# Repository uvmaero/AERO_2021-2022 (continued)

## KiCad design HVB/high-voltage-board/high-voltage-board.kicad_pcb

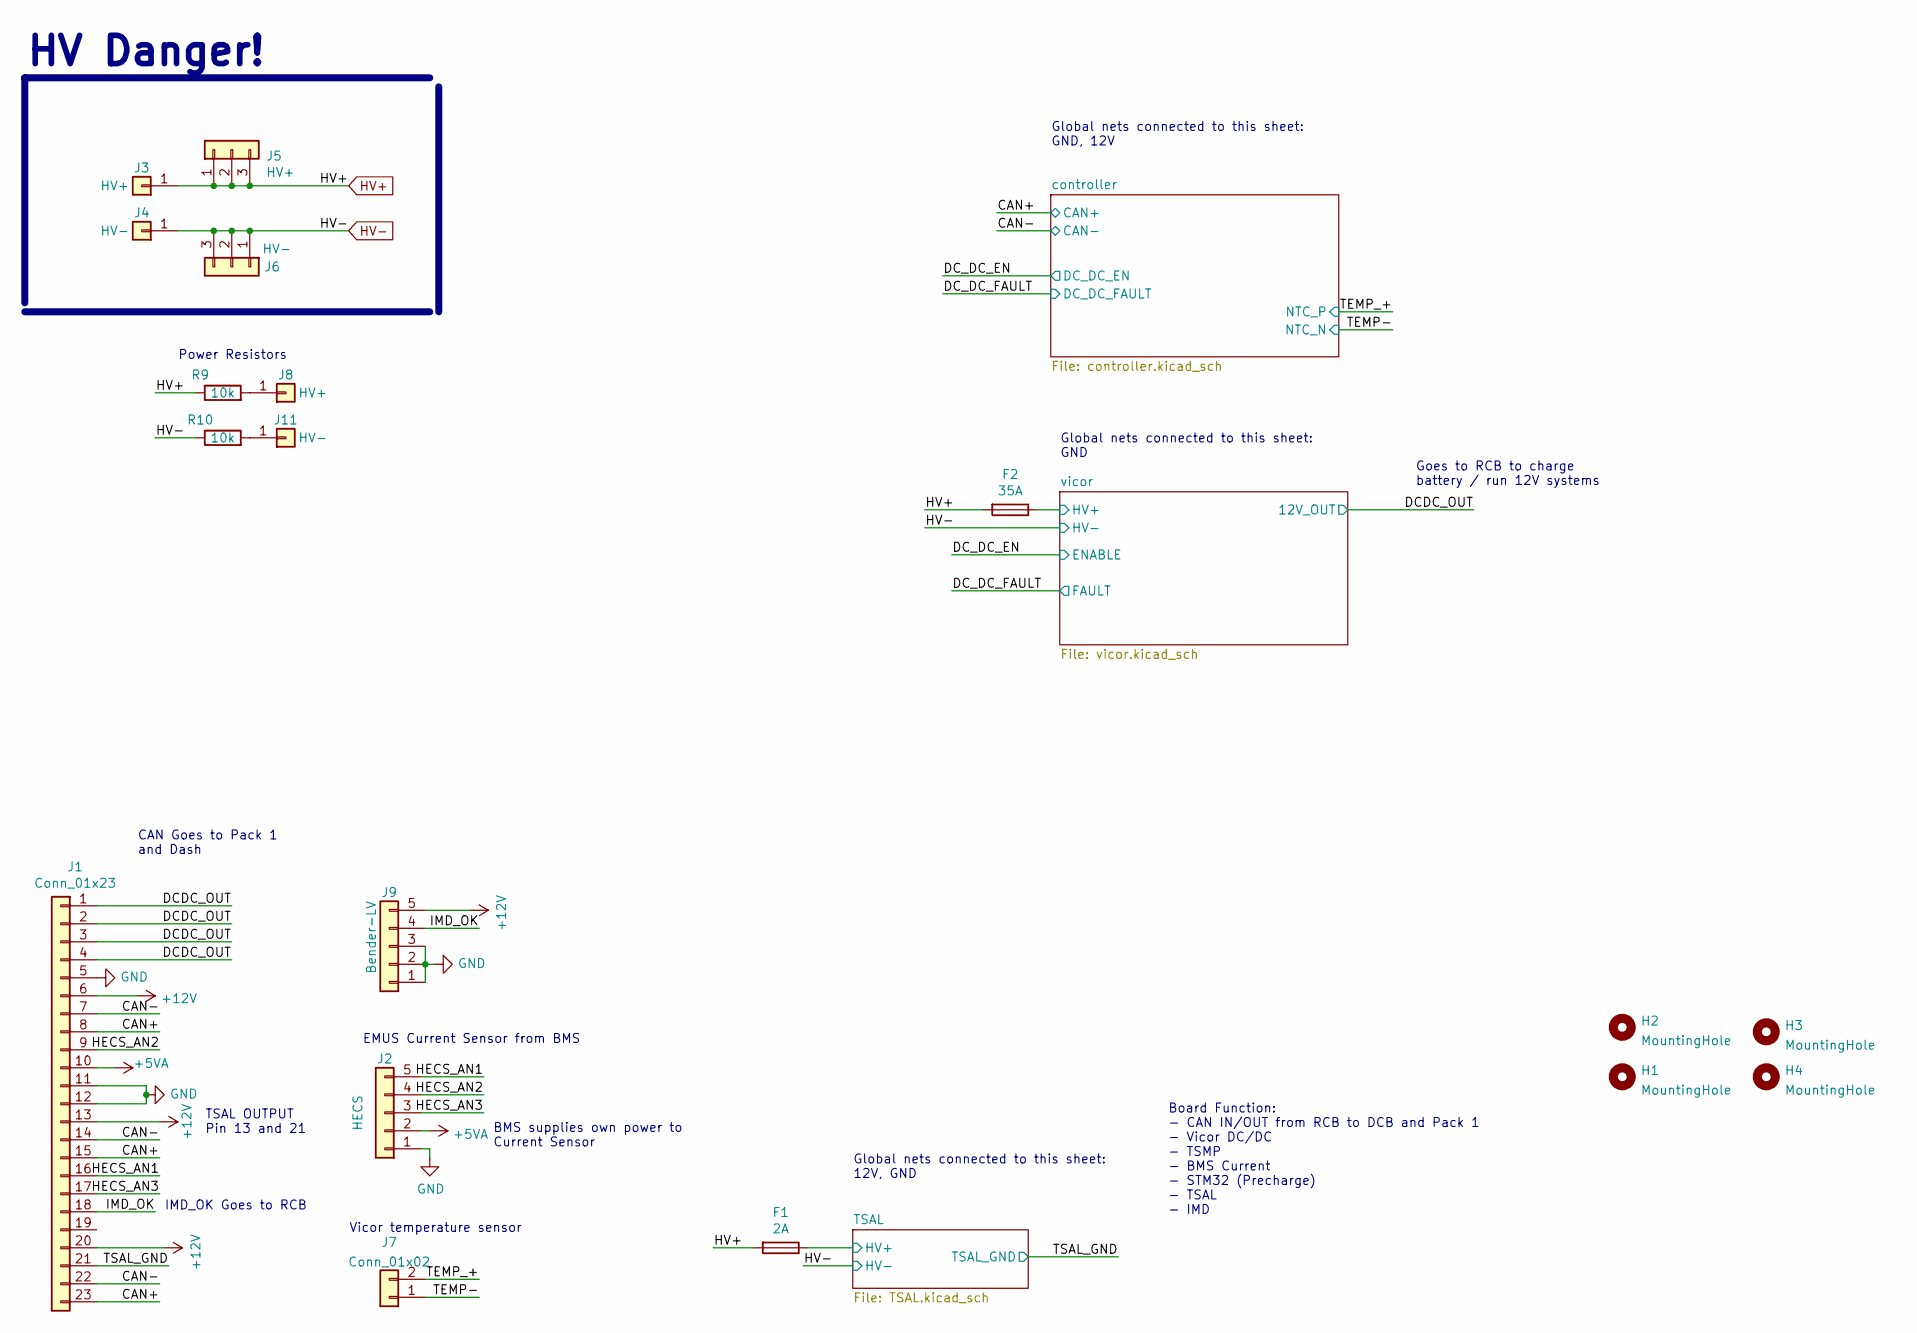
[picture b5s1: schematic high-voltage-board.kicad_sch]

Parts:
F1: 2A; Fuseholder_Cylinder-5x20mm_Schurter_0031_8201_Horizontal_Op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
F2: 35A; Fuseholder_Cylinder-5x20mm_Schurter_0031_8201_Horizontal_Op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
H1, H2, H3, H4: MountingHole; MountingHole_3.2mm_M3
J1: Conn_01x23; TE_1-770669-1_23pin_Horizontal
J2: HECS; JST_XH_B5B-XH-A_1x05_P2.50mm_Vertical
J3, J8: HV+; Hirose_DF63M-1P-3.96DSA_1x01_P3.96mm_Vertical
J4, J11: HV-; Hirose_DF63M-1P-3.96DSA_1x01_P3.96mm_Vertical
J5: HV+; TE_MATE-N-LOK_1-770870-x_1x03_P4.14mm_Vertical
J6: HV-; TE_MATE-N-LOK_1-770870-x_1x03_P4.14mm_Vertical
J7: Conn_01x02; JST_XH_B2B-XH-A_1x02_P2.50mm_Vertical
J9: Bender-LV; JST_XH_B5B-XH-A_1x05_P2.50mm_Vertical
R9, R10: 10k; R_Axial_Power_L50.0mm_W9.0mm_P60.96mm

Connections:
+3V3: J7.2; also elsewhere on the board
+5VA: J1.10, J2.2
+12V: J1.6, J1.13, J1.20, J9.5; also elsewhere on the board
/CAN+: J1.8, J1.15, J1.23; also elsewhere on the board
/CAN-: J1.7, J1.14, J1.22; also elsewhere on the board
/DCDC_OUT: J1.1, J1.2, J1.3, J1.4; also elsewhere on the board
/HECS_AN1: J1.16, J2.5
/HECS_AN2: J1.9, J2.4
/HECS_AN3: J1.17, J2.3
/IMD_OK: J1.18, J9.4
/TEMP-: J7.1; also elsewhere on the board
/TSAL/HV+: F1.1; also elsewhere on the board
/TSAL_GND: J1.21; also elsewhere on the board
/vicor/HV+: F2.1; also elsewhere on the board
GND: J1.5, J1.11, J1.12, J2.1, J9.1, J9.2, J9.3; also elsewhere on the board
HV+: F1.2, F2.2, J3.1, J5.1, J5.2, J5.3, R9.1
HV-: J4.1, J6.1, J6.2, J6.3, R10.1; also elsewhere on the board
unnamed: J8.1, R9.2
unnamed: J11.1, R10.2

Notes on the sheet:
Global nets connected to this sheet: GND, 12V
Global nets connected to this sheet: 12V, GND
IMD_OK Goes to RCB
Goes to RCB to charge battery / run 12V systems
TSAL OUTPUT Pin 13 and 21
Board Function: - CAN IN/OUT from RCB to DCB and Pack 1 - Vicor DC/DC - TSMP - BMS Current - STM32 (Precharge) - TSAL - IMD
Power Resistors
Vicor temperature sensor
EMUS Current Sensor from BMS
CAN Goes to Pack 1 and Dash
Global nets connected to this sheet: GND
HV Danger!
BMS supplies own power to Current Sensor

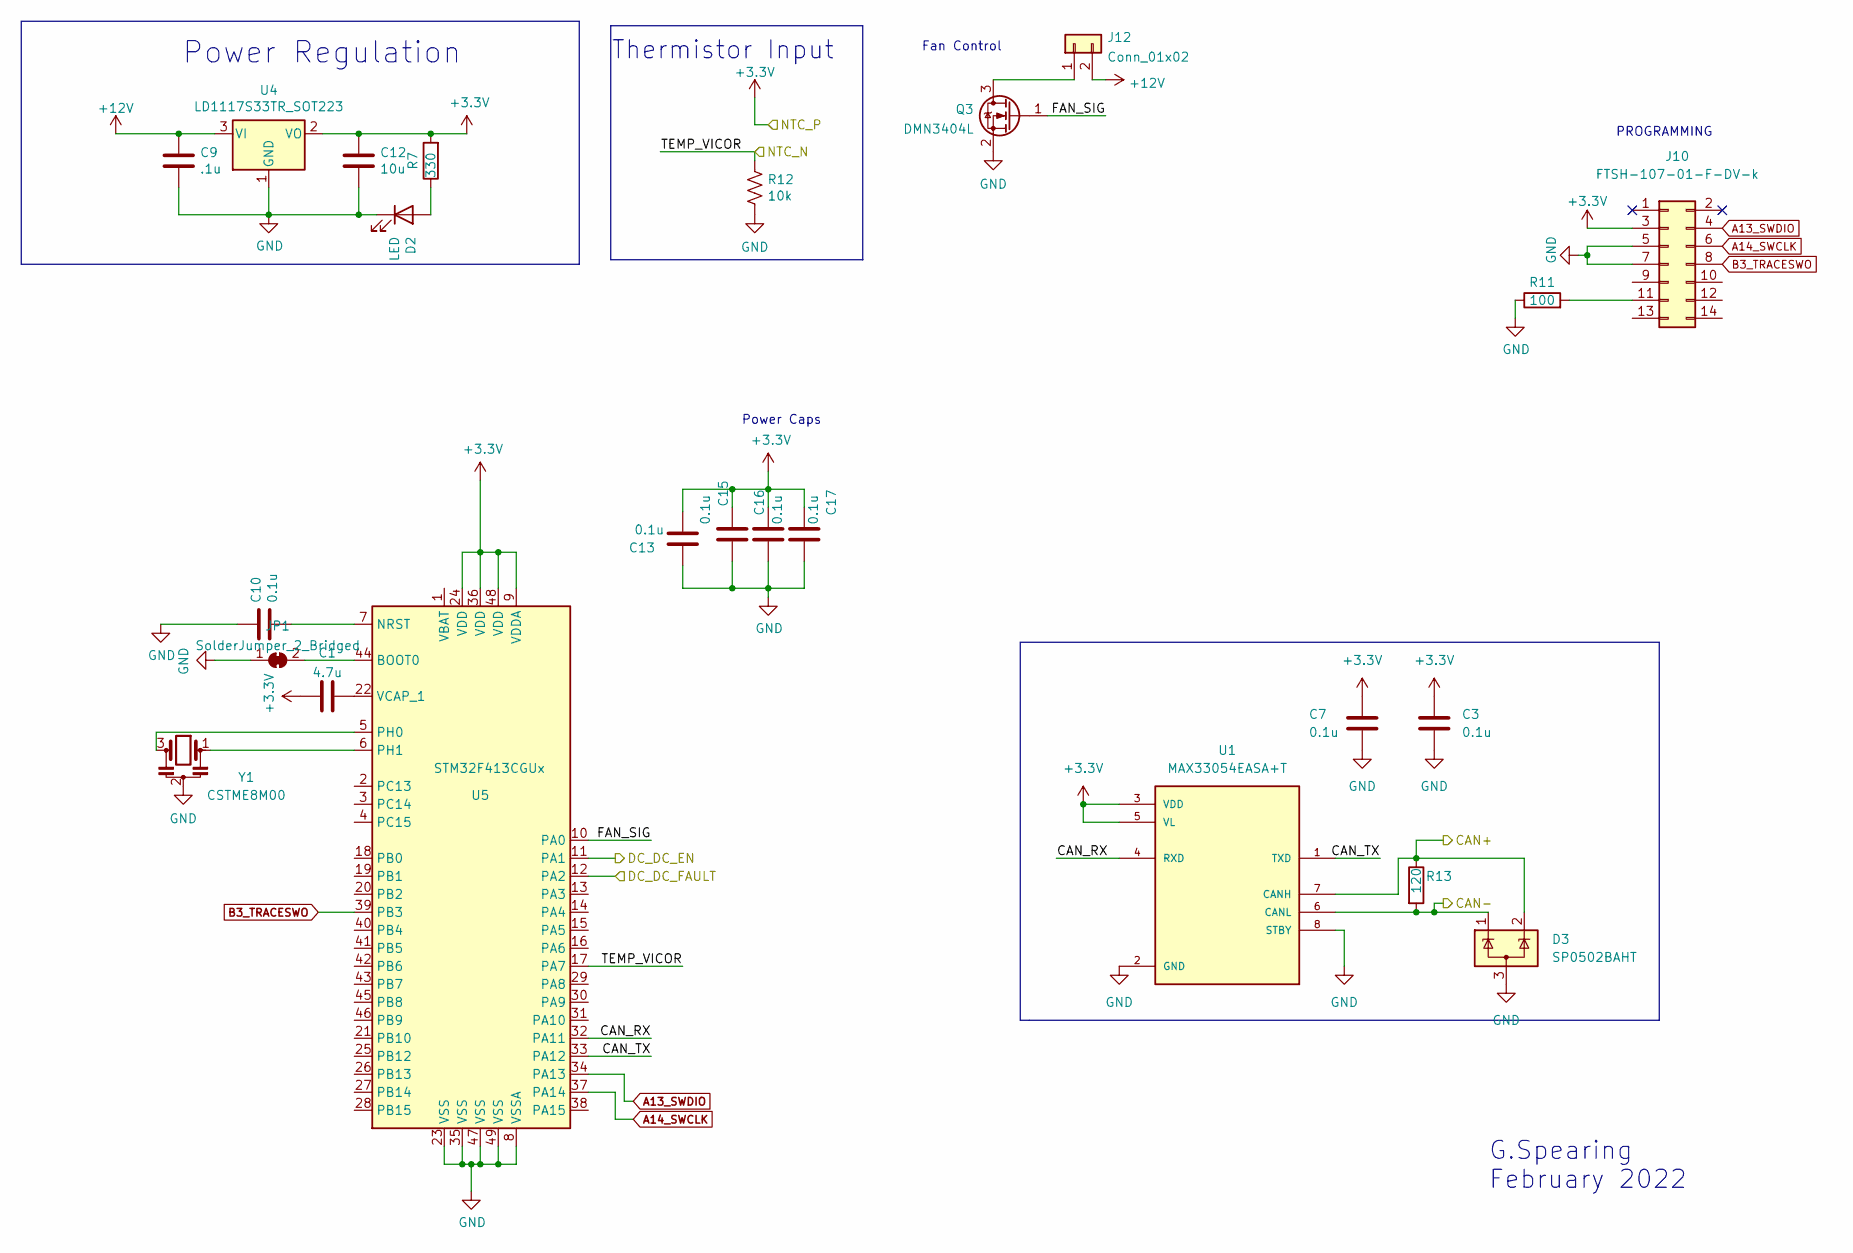
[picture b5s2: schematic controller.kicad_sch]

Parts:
C1: 4.7u; C_0603_1608Metric_Pad1.08x0.95mm_HandSolder
C3, C7, C10, C13, C15, C16, C17: 0.1u; C_0603_1608Metric_Pad1.08x0.95mm_HandSolder
C9: .1u; C_0603_1608Metric_Pad1.08x0.95mm_HandSolder
C12: 10u; C_0603_1608Metric_Pad1.08x0.95mm_HandSolder
D2: LED; LED_0603_1608Metric_Pad1.05x0.95mm_HandSolder
D3: SP0502BAHT; SOT-23
J10: FTSH-107-01-F-DV-k; PinHeader_2x07_P1.27mm_Vertical_SMD
J12: Conn_01x02; JST_XH_B2B-XH-A_1x02_P2.50mm_Vertical
JP1: SolderJumper_2_Bridged; SolderJumper-2_P1.3mm_Bridged_RoundedPad1.0x1.5mm
Q3: DMN3404L; SOT-23_Handsoldering
R7: 330; R_0603_1608Metric_Pad0.98x0.95mm_HandSolder
R11: 100; R_0603_1608Metric_Pad0.98x0.95mm_HandSolder
R12: 10k; R_0603_1608Metric_Pad0.98x0.95mm_HandSolder
R13: 120; R_0603_1608Metric_Pad0.98x0.95mm_HandSolder
U1: MAX33054EASA+T; SOIC127P600X175-8N
U4: LD1117S33TR_SOT223; SOT-223-3_TabPin2
U5: STM32F413CGUx; QFN-48-1EP_7x7mm_P0.5mm_EP5.3x5.3mm
Y1: CSTME8M00; Resonator_SMD_muRata_CSTxExxV-3Pin_3.0x1.1mm_HandSoldering

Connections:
+3V3: C1.1, C3.1, C7.1, C12.1, C13.2, C15.1, C16.1, C17.1, J10.3, R7.2, U1.3 (VDD), U1.5 (VL), U4.2 (VO), U5.9 (VDDA), U5.24 (VDD), U5.36 (VDD), U5.48 (VDD); also elsewhere on the board
+12V: C9.1, J12.2, U4.3 (VI); also elsewhere on the board
/CAN+: D3.2 (K), R13.1, U1.7 (CANH); also elsewhere on the board
/CAN-: D3.1 (K), R13.2, U1.6 (CANL); also elsewhere on the board
/DC_DC_EN: U5.11 (PA1); also elsewhere on the board
/DC_DC_FAULT: U5.12 (PA2); also elsewhere on the board
/TEMP-: R12.2, U5.17 (PA7); also elsewhere on the board
/controller/CAN_RX: U1.4 (RXD), U5.32 (PA11)
/controller/CAN_TX: U1.1 (TXD), U5.33 (PA12)
/controller/FAN_SIG: Q3.1 (G), U5.10 (PA0)
A13_SWDIO: J10.4, U5.34 (PA13)
A14_SWCLK: J10.6, U5.37 (PA14)
B3_TRACESWO: J10.8, U5.39 (PB3)
GND: C3.2, C7.2, C9.2, C10.1, C12.2, C13.1, C15.2, C16.2, C17.2, D2.1 (K), D3.3 (A), J10.5, J10.7, JP1.1 (A), Q3.2 (S), R11.1, R12.1, U1.2 (GND), U1.8 (STBY), U4.1 (GND), U5.8 (VSSA), U5.23 (VSS), U5.35 (VSS), U5.47 (VSS), U5.49 (VSS), Y1.2; also elsewhere on the board
unnamed: C1.2, U5.22 (VCAP_1)
unnamed: C10.2, U5.7 (NRST)
unnamed: D2.2 (A), R7.1
unnamed: J10.11, R11.2
unnamed: J12.1, Q3.3 (D)
unnamed: JP1.2 (B), U5.44 (BOOT0)
unnamed: U5.5 (PH0), Y1.3
unnamed: U5.6 (PH1), Y1.1

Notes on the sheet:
G.Spearing February 2022
Fan Control
PROGRAMMING
Thermistor Input
Power Caps
Power Regulation

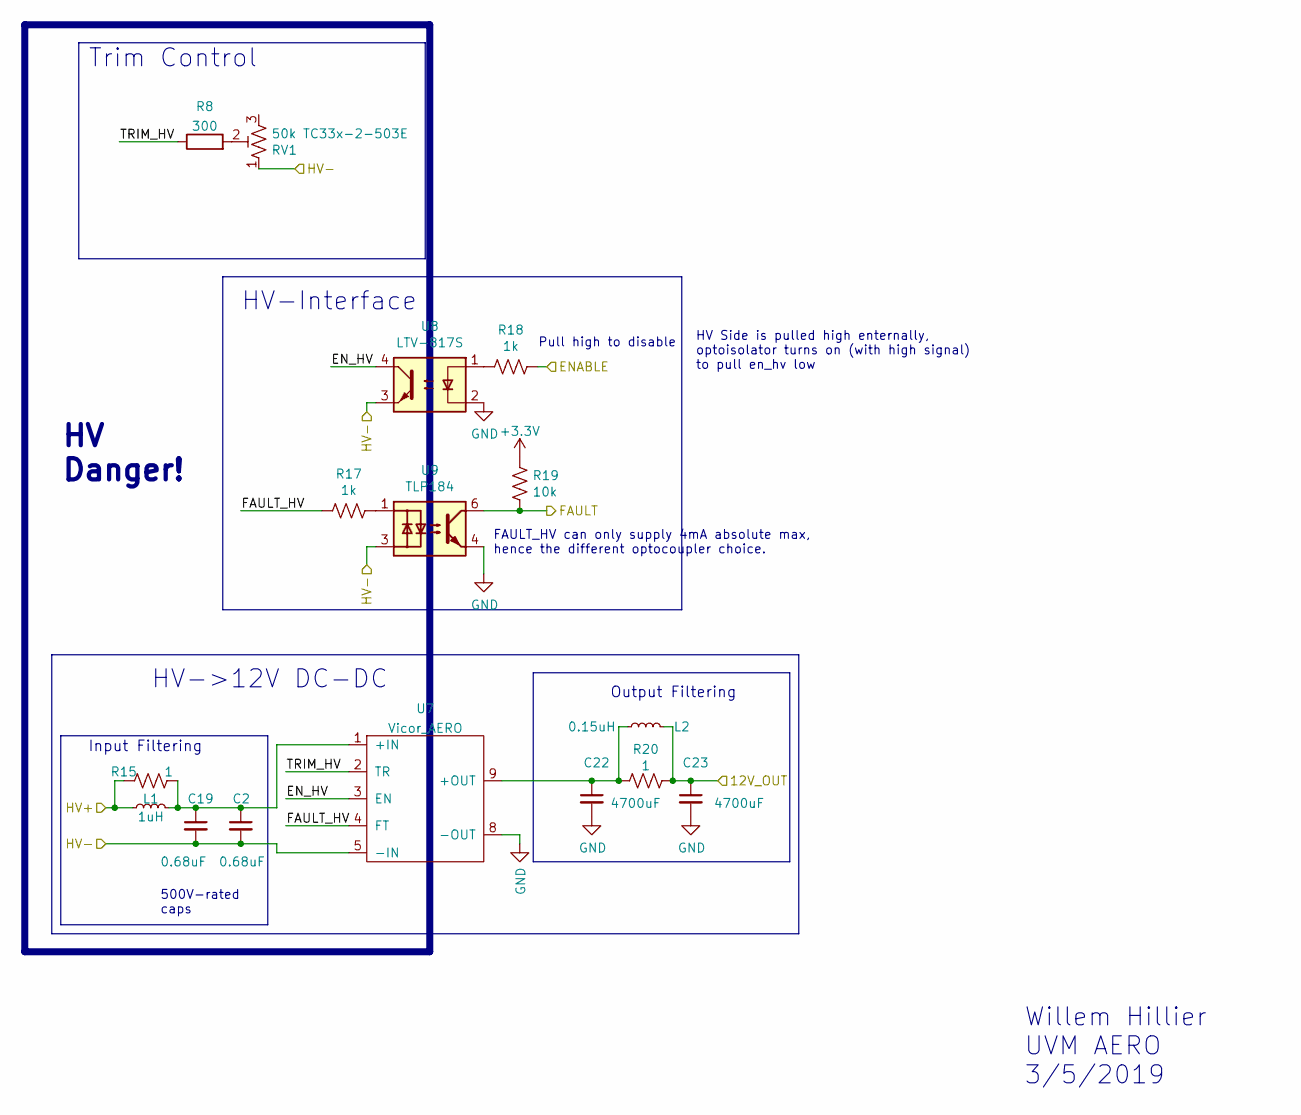
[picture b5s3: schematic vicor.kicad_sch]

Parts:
C2, C19: 0.68uF; C_Rect_L18.0mm_W8.0mm_P15.00mm_FKS3_FKP3
C22, C23: 4700uF; C_Radial_D18.0mm_H35.5mm_P7.50mm
L1: 1uH; L_1008_2520Metric_Pad1.43x2.20mm_HandSolder
L2: 0.15uH; L_0805_2012Metric_Pad1.15x1.40mm_HandSolder
R8: 300; R_0603_1608Metric_Pad0.98x0.95mm_HandSolder
R15, R20: 1; R_2512_6332Metric_Pad1.40x3.35mm_HandSolder
R17, R18: 1k; R_0603_1608Metric_Pad0.98x0.95mm_HandSolder
R19: 10k; R_0603_1608Metric_Pad0.98x0.95mm_HandSolder
RV1: 50k TC33x-2-503E; Potentiometer_Bourns_TC33X_Vertical
U7: Vicor_AERO; vicor-socket-no-cutouts
U8: LTV-817S; SMDIP-4_W9.53mm_Clearance8mm
U9: TLP184; MFSOP6-4_4.4x3.6mm_P1.27mm

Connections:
+3V3: R19.2; also elsewhere on the board
/DCDC_OUT: C23.1, L2.2, R20.1; also elsewhere on the board
/DC_DC_EN: R18.1; also elsewhere on the board
/DC_DC_FAULT: R19.1, U9.6; also elsewhere on the board
/vicor/EN_HV: U7.3 (EN), U8.4
/vicor/FAULT_HV: R17.2, U7.4 (FT)
/vicor/HV+: L1.1, R15.2; also elsewhere on the board
/vicor/TRIM_HV: R8.1, U7.2 (TR)
GND: C22.2, C23.2, U7.8 (-OUT), U8.2, U9.4; also elsewhere on the board
HV-: C2.2, C19.2, RV1.1, U7.5 (-IN), U8.3, U9.3; also elsewhere on the board
unnamed: C2.1, C19.1, L1.2, R15.1, U7.1 (+IN)
unnamed: C22.1, L2.1, R20.2, U7.9 (+OUT)
unnamed: R8.2, RV1.2
unnamed: R17.1, U9.1
unnamed: R18.2, U8.1

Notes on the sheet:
Output Filtering
500V-rated caps
Willem Hillier UVM AERO 3/5/2019
Input Filtering
Trim Control
HV-Interface
Pull high to disable
HV->12V DC-DC
HV Side is pulled high enternally, optoisolator turns on (with high signal) to pull en_hv low
HV Danger!
FAULT_HV can only supply 4mA absolute max, hence the different optocoupler choice.

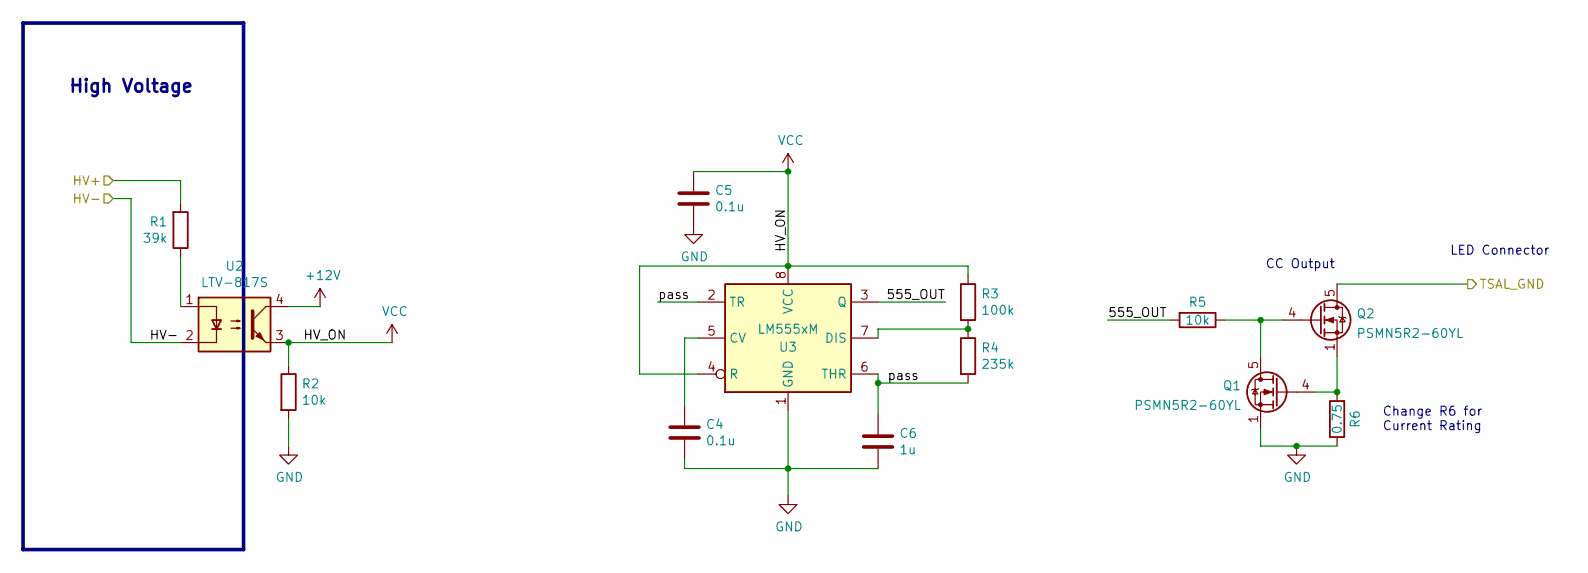
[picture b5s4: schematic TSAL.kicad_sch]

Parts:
C4, C5: 0.1u; C_0603_1608Metric_Pad1.08x0.95mm_HandSolder
C6: 1u; C_0603_1608Metric_Pad1.08x0.95mm_HandSolder
Q1, Q2: PSMN5R2-60YL; LFPAK56
R1: 39k; R_Axial_DIN0411_L9.9mm_D3.6mm_P25.40mm_Horizontal
R2, R5: 10k; R_0603_1608Metric_Pad0.98x0.95mm_HandSolder
R3: 100k; R_0603_1608Metric_Pad0.98x0.95mm_HandSolder
R4: 235k; R_0603_1608Metric_Pad0.98x0.95mm_HandSolder
R6: 0.75; R_2512_6332Metric_Pad1.40x3.35mm_HandSolder
U2: LTV-817S; SMDIP-4_W9.53mm_Clearance8mm
U3: LM555xM; SOIC-8_3.9x4.9mm_P1.27mm

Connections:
+12V: U2.4; also elsewhere on the board
/TSAL/555_OUT: R5.2, U3.3 (Q)
/TSAL/HV+: R1.2; also elsewhere on the board
/TSAL/pass: C6.1, R4.2, U3.2 (TR), U3.6 (THR)
/TSAL_GND: Q2.5 (D); also elsewhere on the board
GND: C4.2, C5.2, C6.2, Q1.1 (S), Q1.2 (S), Q1.3 (S), R2.2, R6.1, U3.1 (GND); also elsewhere on the board
HV-: U2.2; also elsewhere on the board
unnamed: C4.1, U3.5 (CV)
unnamed: Q1.4 (G), Q2.1 (S), Q2.2 (S), Q2.3 (S), R6.2
unnamed: Q1.5 (D), Q2.4 (G), R5.1
unnamed: R1.1, U2.1
unnamed: R3.2, R4.1, U3.7 (DIS)
VCC: C5.1, R2.1, R3.1, U2.3, U3.4 (R), U3.8 (VCC)

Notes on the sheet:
Change R6 for Current Rating
CC Output
LED Connector
High Voltage

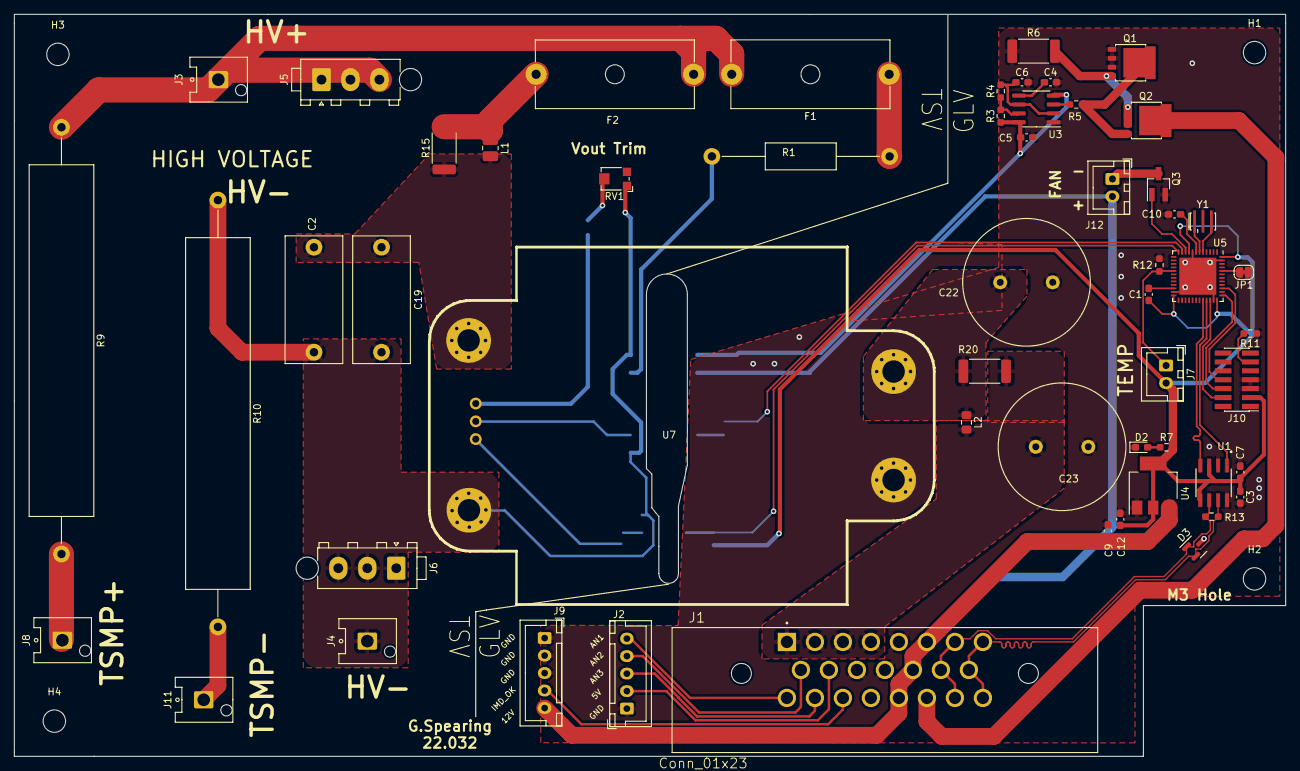
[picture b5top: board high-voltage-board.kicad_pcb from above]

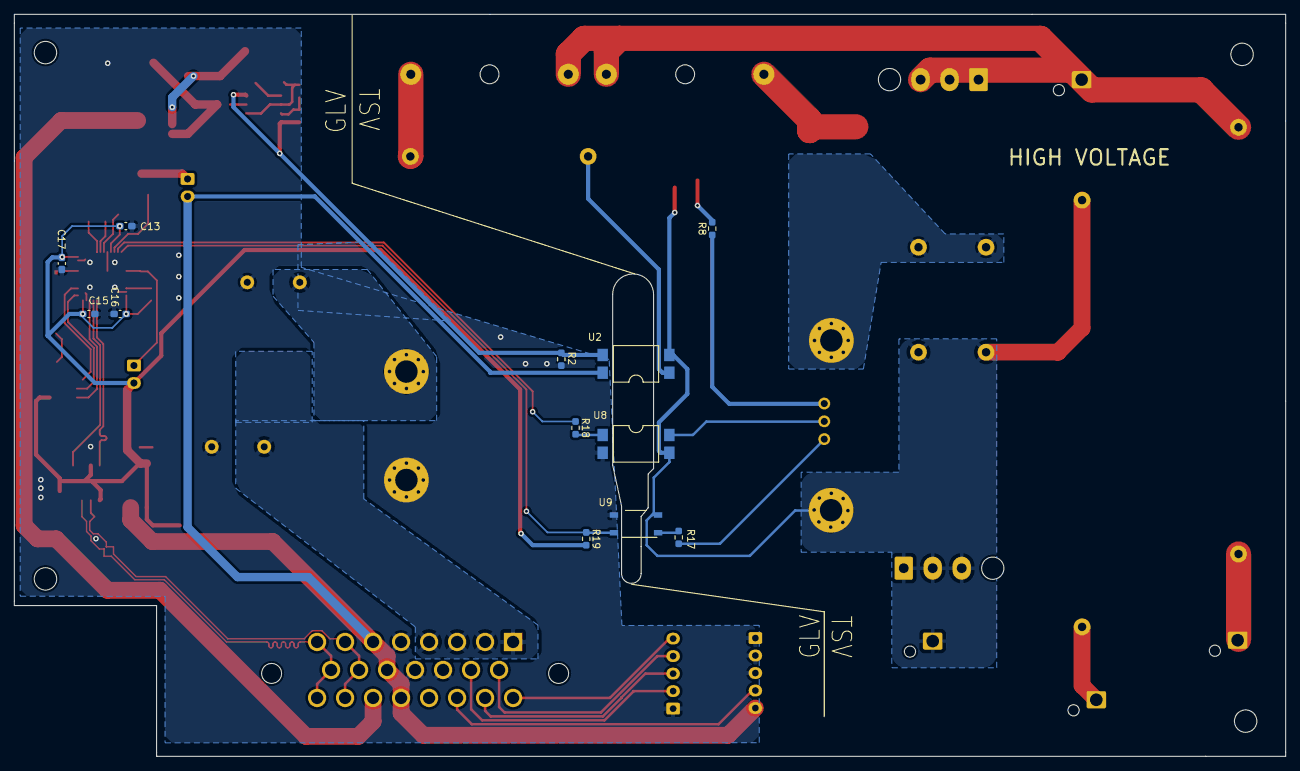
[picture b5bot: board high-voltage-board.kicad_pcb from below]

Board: 2 copper layers, 181.6 x 106.0 mm, 71 parts (12 on the bottom side), 51 nets.

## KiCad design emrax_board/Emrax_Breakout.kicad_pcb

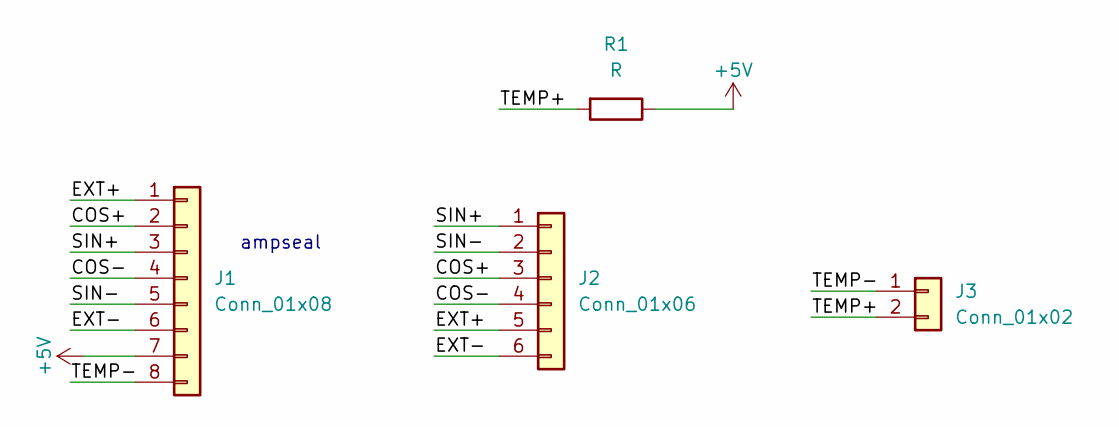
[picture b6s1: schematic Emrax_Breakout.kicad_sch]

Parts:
J1: Conn_01x08; TE_1-776280-1_8pin_Horizontal
J2: Conn_01x06; JST_XH_S6B-XH-A-1_1x06_P2.50mm_Horizontal
J3: Conn_01x02; JST_XH_S2B-XH-A-1_1x02_P2.50mm_Horizontal
R1: R; R_0603_1608Metric_Pad0.98x0.95mm_HandSolder

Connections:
+5V: J1.7, R1.1
/COS+: J1.2, J2.3
/COS-: J1.4, J2.4
/EXT+: J1.1, J2.5
/EXT-: J1.6, J2.6
/SIN+: J1.3, J2.1
/SIN-: J1.5, J2.2
/TEMP+: J3.2, R1.2
/TEMP-: J1.8, J3.1

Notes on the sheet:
ampseal

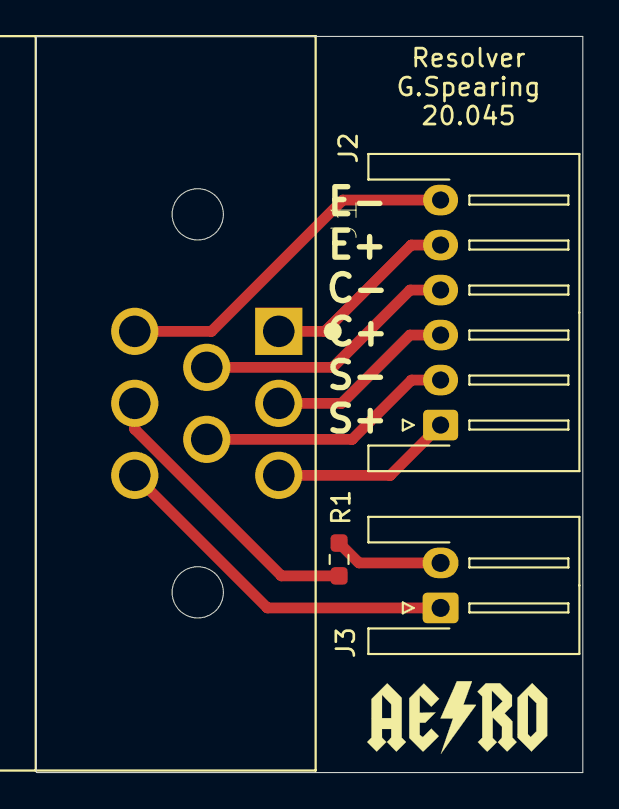
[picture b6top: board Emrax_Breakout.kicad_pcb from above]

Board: 2 copper layers, 30.4 x 40.9 mm, 4 parts (0 on the bottom side), 9 nets.

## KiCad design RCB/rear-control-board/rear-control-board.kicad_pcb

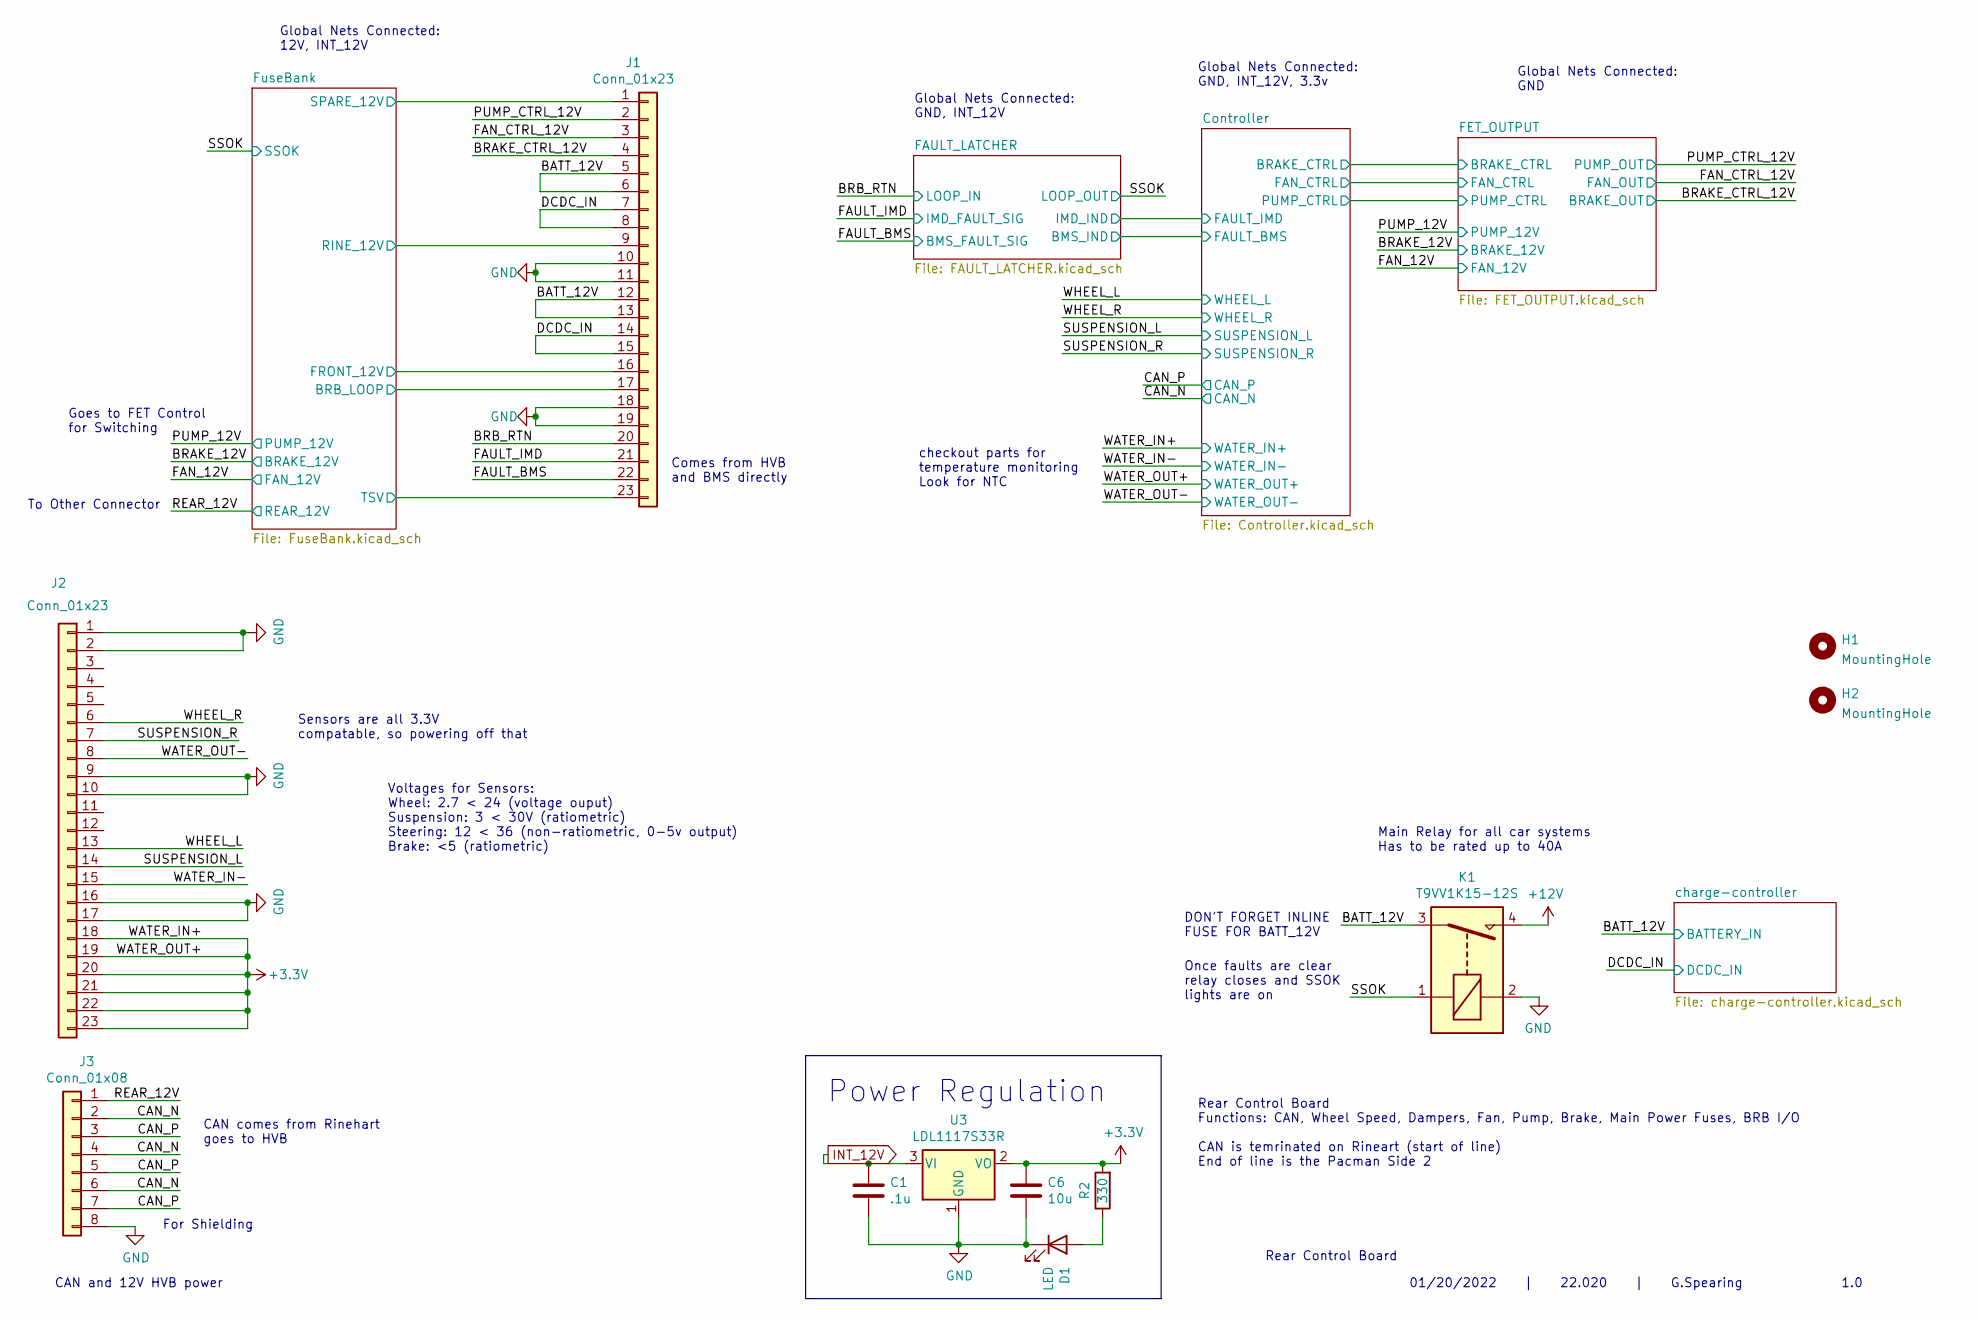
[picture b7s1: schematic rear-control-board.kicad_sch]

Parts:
C1: .1u; C_0603_1608Metric_Pad1.08x0.95mm_HandSolder
C6: 10u; C_0603_1608Metric_Pad1.08x0.95mm_HandSolder
D1: LED; LED_0603_1608Metric_Pad1.05x0.95mm_HandSolder
H1, H2: MountingHole; MountingHole_3.2mm_M3
J1, J2: Conn_01x23; TE_1-770669-1_23pin_Horizontal
J3: Conn_01x08; TE_1-776280-1_8pin_Horizontal
K1: T9VV1K15-12S; RELAY_T9VV1K15-12S
R2: 330; R_0603_1608Metric_Pad0.98x0.95mm_HandSolder
U3: LDL1117S33R; SOT-223-3_TabPin2

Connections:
+3V3: C6.1, J2.18, J2.19, J2.20, J2.21, J2.22, J2.23, R2.2, U3.2 (VO); also elsewhere on the board
+12V: K1.4; also elsewhere on the board
/BATT_12V: J1.5, J1.6, J1.12, J1.13, K1.3; also elsewhere on the board
/BRAKE_CTRL_12V: J1.4; also elsewhere on the board
/BRB_RTN: J1.20; also elsewhere on the board
/CAN_N: J3.2, J3.4, J3.6; also elsewhere on the board
/CAN_P: J3.3, J3.5, J3.7; also elsewhere on the board
/DCDC_IN: J1.7, J1.8, J1.14, J1.15; also elsewhere on the board
/FAN_CTRL_12V: J1.3; also elsewhere on the board
/FAULT_BMS: J1.22; also elsewhere on the board
/FAULT_IMD: J1.21; also elsewhere on the board
/FuseBank/BRB_LOOP: J1.17; also elsewhere on the board
/FuseBank/FRONT_12V: J1.16; also elsewhere on the board
/FuseBank/RINE_12V: J1.9; also elsewhere on the board
/FuseBank/SPARE_12V: J1.1; also elsewhere on the board
/FuseBank/TSV: J1.23; also elsewhere on the board
/PUMP_CTRL_12V: J1.2; also elsewhere on the board
/REAR_12V: J3.1; also elsewhere on the board
/SSOK: K1.1; also elsewhere on the board
/SUSPENSION_L: J2.14; also elsewhere on the board
/SUSPENSION_R: J2.7; also elsewhere on the board
/WATER_IN-: J2.15; also elsewhere on the board
/WATER_OUT-: J2.8; also elsewhere on the board
/WHEEL_L: J2.13; also elsewhere on the board
/WHEEL_R: J2.6; also elsewhere on the board
GND: C1.2, C6.2, D1.1 (K), J1.10, J1.11, J1.18, J1.19, J2.1, J2.2, J2.9, J2.10, J2.16, J2.17, J3.8, K1.2, U3.1 (GND); also elsewhere on the board
INT_12V: C1.1, U3.3 (VI); also elsewhere on the board
unnamed: D1.2 (A), R2.1

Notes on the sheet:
Once faults are clear relay closes and SSOK lights are on
1.0
Comes from HVB and BMS directly
Global Nets Connected: GND
Main Relay for all car systems Has to be rated up to 40A
checkout parts for temperature monitoring Look for NTC
Global Nets Connected: GND, INT_12V
Voltages for Sensors: Wheel: 2.7 < 24 (voltage ouput) Suspension: 3 < 30V (ratiometric) Steering: 12 < 36 (non-ratiometric, 0-5v output) Brake: <5 (ratiometric)
DON'T FORGET INLINE FUSE FOR BATT_12V
01/20/2022 | 22.020 | G.Spearing
CAN and 12V HVB power
Rear Control Board Functions: CAN, Wheel Speed, Dampers, Fan, Pump, Brake, Main Power Fuses, BRB I/O CAN is temrinated on Rineart (start of line) End of line is the Pacman Side 2
Goes to FET Control for Switching
To Other Connector
CAN comes from Rinehart goes to HVB
For Shielding
Power Regulation
Global Nets Connected: GND, INT_12V, 3.3v
Sensors are all 3.3V compatable, so powering off that
Global Nets Connected: 12V, INT_12V
Rear Control Board
